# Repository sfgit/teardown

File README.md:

# teardown
Files from Crowdsupply Teardown 2018 EAGLE Presentation

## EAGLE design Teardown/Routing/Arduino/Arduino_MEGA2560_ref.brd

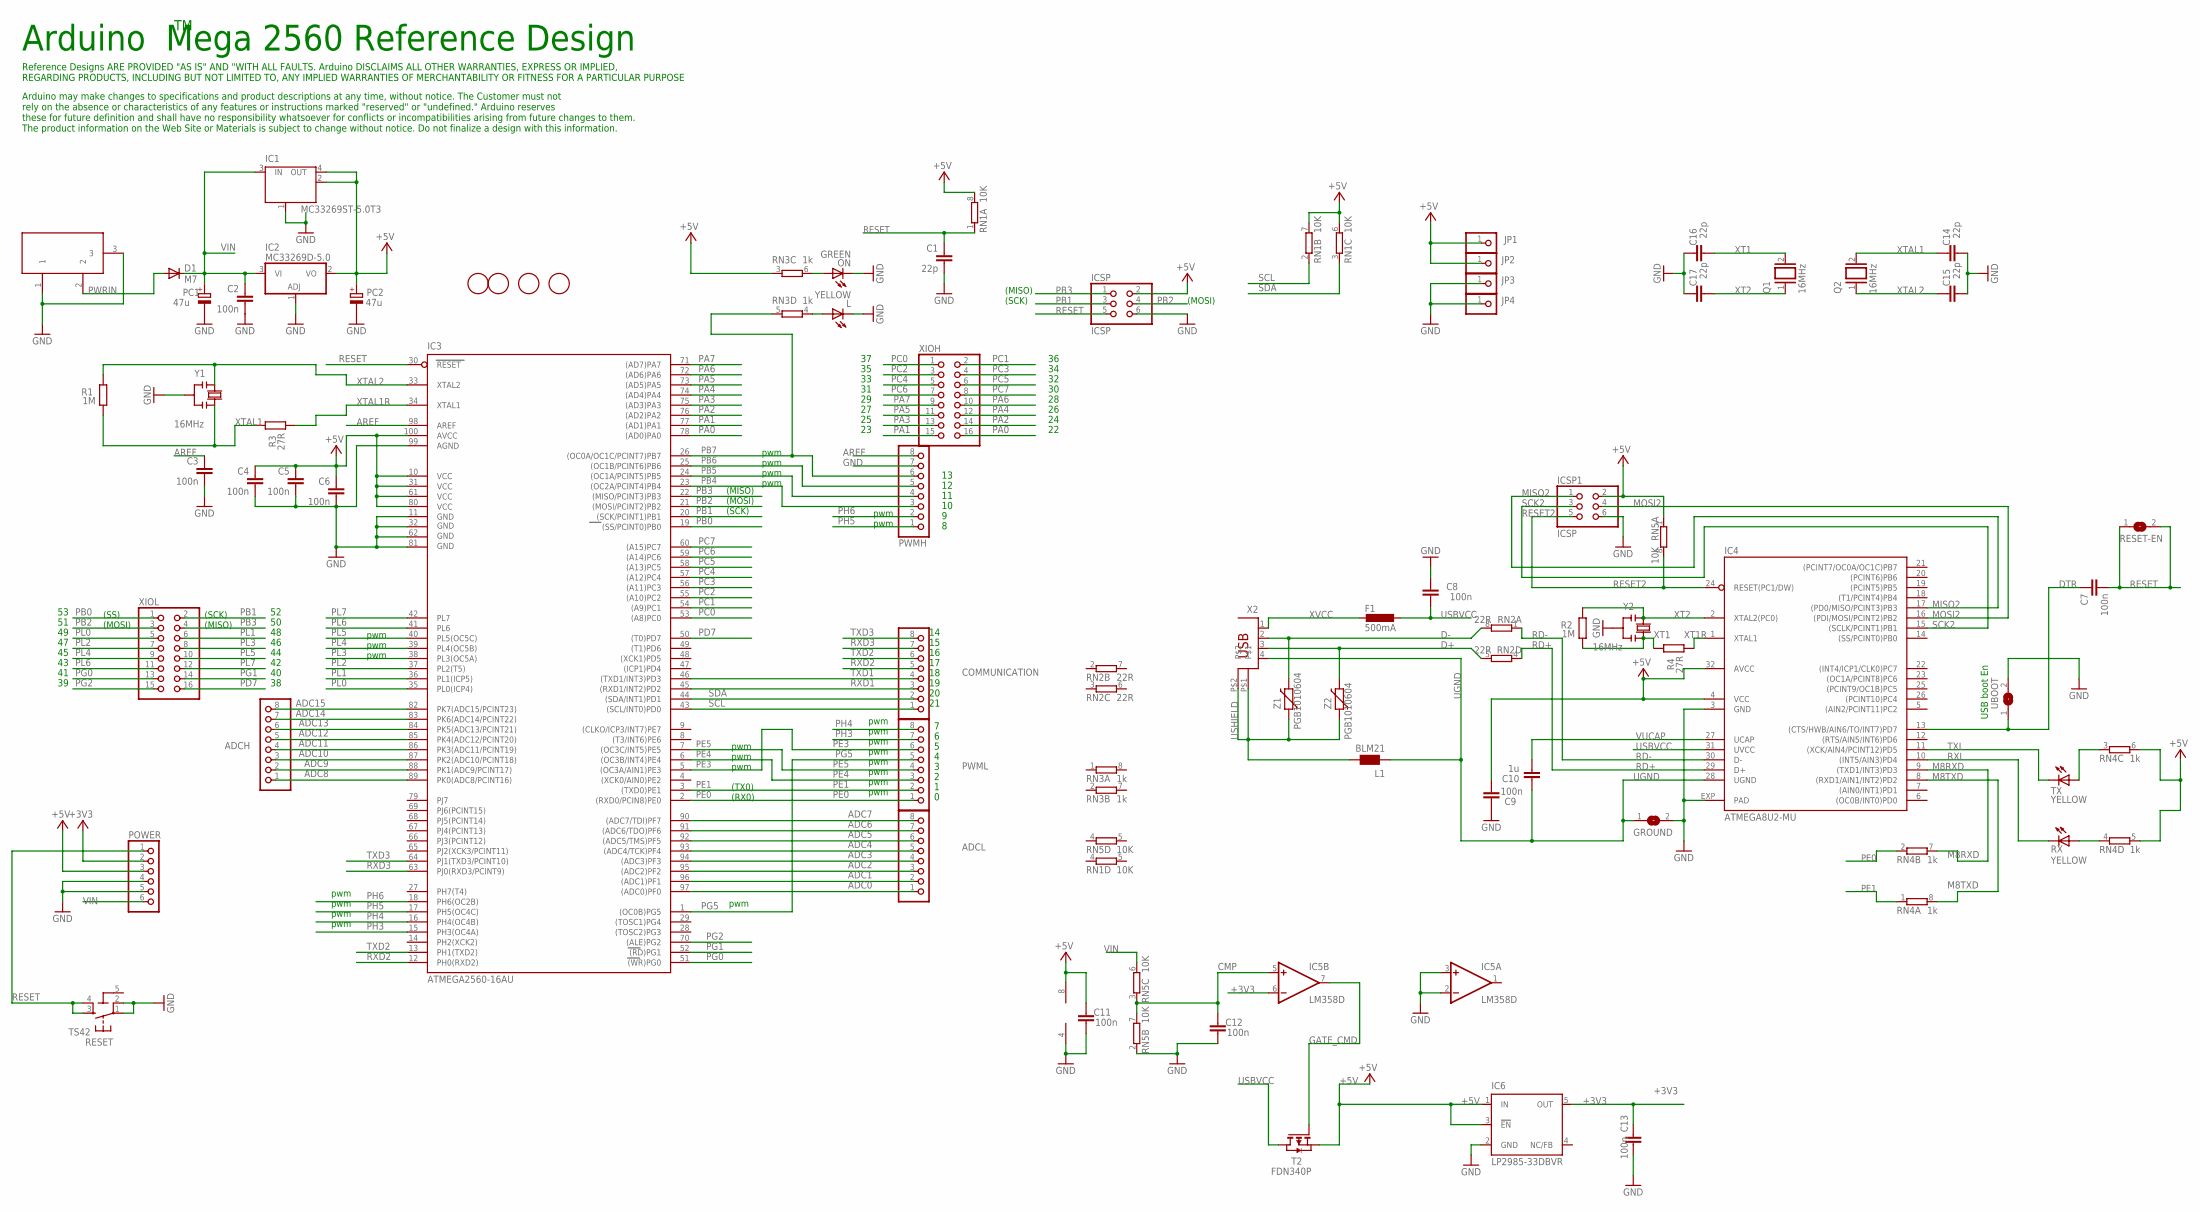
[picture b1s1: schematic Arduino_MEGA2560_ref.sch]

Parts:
ADCH: PINHD-1X8; 1X08
ADCL: PINHD-1X8; 1X08
C1, C14, C15, C16, C17: 22p; C0603-ROUND
C2, C3, C4, C5, C6, C7, C9, C12, C13: 100n; C0603-ROUND
C8, C11: 100n; C0603
C10: 1u; C0603-ROUND
COMMUNICATION: PINHD-1X8; 1X08
D1: M7; SMB
F1: 500mA; L1812
GROUND: SJ
IC1: MC33269ST-5.0T3; SOT223
IC2: MC33269D-5.0; DPACK
IC3: ATMEGA2560-16AU; TQFP100
IC4: ATMEGA8U2-MU; QFN32
IC5: LM358D; SO08
IC6: LP2985-33DBVR; SOT23-DBV
ICSP, ICSP1: ICSP; 2X03
JP1, JP2, JP3, JP4: PINHD-1X1; 1X01
L: YELLOW; CHIP-LED0805
L1: BLM21; 0805
ON: GREEN; CHIP-LED0805
PC1, PC2: 47u; PANASONIC_D
POWER: PINHD-1X6; 1X06
PWMH: PINHD-1X8; 1X08
PWML: PINHD-1X8; 1X08
Q1, Q2: 16MHz; QS
R1, R2: 1M; R0603-ROUND
R3, R4: 27R; R0603-ROUND
RESET: TS42
RESET-EN: SJ
RN1, RN5: 10K; CAT16
RN2: 22R; CAY16
RN3, RN4: 1k; CAY16
RX: YELLOW; CHIP-LED0805
T2: FDN340P; SOT-23
TX: YELLOW; CHIP-LED0805
U$2, U$3, U$4, U$5: FIDUCIALMOUNT; FIDUCIA-MOUNT
UBOOT: SJ
X1: DC21MMX; DC-21MM
X2: PN61729
XIOH: PINHD-2X8; 2X08
XIOL: PINHD-2X8; 2X08
Y1, Y2: 16MHz; RESONATOR
Z1, Z2: PGB1010604; CT/CN0603

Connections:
5-GND: RESET.5 (5-GND)
+3V3: C13.2, IC5.6 (-IN), IC6.5 (OUT), POWER.2
+5V: C4.1, C5.1, C6.1, C9.1, C11.2, IC1.2 (OUT), IC1.4 (OUT), IC2.2 (VO), IC3.10 (VCC), IC3.31 (VCC1), IC3.61 (VCC2), IC3.80 (VCC3), IC3.100 (AVCC), IC4.4 (VCC), IC4.32 (AVCC), IC5.8 (V+), IC6.1 (IN), IC6.3 (!EN), ICSP.2, ICSP1.2, JP1.1, JP2.1, PC2.+, POWER.3, RN1.6 (2), RN1.7 (2), RN1.8 (2), RN3.3 (1), RN4.5 (2), RN4.6 (2), RN5.1, T2.2 (S)
ADC0: ADCL.1, IC3.97 ((ADC0)PF0)
ADC1: ADCL.2, IC3.96 ((ADC1)PF1)
ADC2: ADCL.3, IC3.95 ((ADC2)PF2)
ADC3: ADCL.4, IC3.94 ((ADC3)PF3)
ADC4: ADCL.5, IC3.93 ((ADC4/TCK)PF4)
ADC5: ADCL.6, IC3.92 ((ADC5/TMS)PF5)
ADC6: ADCL.7, IC3.91 ((ADC6/TDO)PF6)
ADC7: ADCL.8, IC3.90 ((ADC7/TDI)PF7)
ADC8: ADCH.1, IC3.89 (PK0(ADC8/PCINT16))
ADC9: ADCH.2, IC3.88 (PK1(ADC9/PCINT17))
ADC10: ADCH.3, IC3.87 (PK2(ADC10/PCINT18))
ADC11: ADCH.4, IC3.86 (PK3(ADC11/PCINT19))
ADC12: ADCH.5, IC3.85 (PK4(ADC12/PCINT20))
ADC13: ADCH.6, IC3.84 (PK5(ADC13/PCINT21))
ADC14: ADCH.7, IC3.83 (PK6(ADC14/PCINT22))
ADC15: ADCH.8, IC3.82 (PK7(ADC15/PCINT23))
AREF: C3.1, IC3.98 (AREF), PWMH.8
CMP: C12.2, IC5.5 (+IN), RN5.3 (1), RN5.7 (2)
D+: RN2.5 (2), X2.3, Z2.2
D-: RN2.8 (2), X2.2, Z1.2
DTR: C7.1, IC4.13 ((CTS/HWB/AIN6/TO/INT7)PD7), UBOOT.1
GATE_CMD: IC5.7 (OUT), T2.3 (G)
GND: C1.2, C2.2, C3.2, C4.2, C5.2, C6.2, C8.2, C9.2, C11.1, C12.1, C13.1, C14.1, C15.1, C16.2, C17.2, GROUND.2, IC1.1 (GND/ADJ), IC2.1 (ADJ), IC3.11 (GND), IC3.32 (GND1), IC3.62 (GND2), IC3.81 (GND3), IC3.99 (AGND), IC4.3 (GND), IC4.EXP (PAD), IC5.2 (-IN), IC5.3 (+IN), IC5.4 (V-), IC6.2 (GND), ICSP.6, ICSP1.6, JP3.1, JP4.1, L.C, ON.C, PC1.-, PC2.-, POWER.4, POWER.5, PWMH.7, RESET.1, RESET.2, RN5.2 (1), UBOOT.2, X1.1, X1.3, Y1.2, Y2.2
M8RXD: IC4.9 ((TXD1/INT3)PD3), RN4.7 (2)
M8TXD: IC4.8 ((RXD1/AIN1/INT2)PD2), RN4.8 (2)
MISO2: IC4.17 ((PD0/MISO/PCINT3)PB3), ICSP1.1
MOSI2: IC4.16 ((PDI/MOSI/PCINT2)PB2), ICSP1.4
unnamed: L.A, RN3.4 (1)
unnamed: ON.A, RN3.6 (2)
unnamed: RN4.4 (1), RX.A
unnamed: RN4.3 (1), TX.A
PA0: IC3.78 ((AD0)PA0), XIOH.16
PA1: IC3.77 ((AD1)PA1), XIOH.15
PA2: IC3.76 ((AD2)PA2), XIOH.14
PA3: IC3.75 ((AD3)PA3), XIOH.13
PA4: IC3.74 ((AD4)PA4), XIOH.12
PA5: IC3.73 ((AD5)PA5), XIOH.11
PA6: IC3.72 ((AD6)PA6), XIOH.10
PA7: IC3.71 ((AD7)PA7), XIOH.9
PB0: IC3.19 ((SS/PCINT0)PB0), XIOL.1
PB1: IC3.20 ((SCK/PCINT1)PB1), ICSP.3, XIOL.2
PB2: IC3.21 ((MOSI/PCINT2)PB2), ICSP.4, XIOL.3
PB3: IC3.22 ((MISO/PCINT3)PB3), ICSP.1, XIOL.4
PB4: IC3.23 ((OC2A/PCINT4)PB4), PWMH.3
PB5: IC3.24 ((OC1A/PCINT5)PB5), PWMH.4
PB6: IC3.25 ((OC1B/PCINT6)PB6), PWMH.5
PB7: IC3.26 ((OC0A/OC1C/PCINT7)PB7), PWMH.6, RN3.5 (2)
PC0: IC3.53 ((A8)PC0), XIOH.1
PC1: IC3.54 ((A9)PC1), XIOH.2
PC2: IC3.55 ((A10)PC2), XIOH.3
PC3: IC3.56 ((A11)PC3), XIOH.4
PC4: IC3.57 ((A12)PC4), XIOH.5
PC5: IC3.58 ((A13)PC5), XIOH.6
PC6: IC3.59 ((A14)PC6), XIOH.7
PC7: IC3.60 ((A15)PC7), XIOH.8
PD7: IC3.50 ((T0)PD7), XIOL.16
PE0: IC3.2 ((RXD0/PCIN8)PE0), PWML.1, RN4.2 (1)
PE1: IC3.3 ((TXD0)PE1), PWML.2, RN4.1
PE3: IC3.5 ((OC3A/AIN1)PE3), PWML.6
PE4: IC3.6 ((OC3B/INT4)PE4), PWML.3
PE5: IC3.7 ((OC3C/INT5)PE5), PWML.4
PG0: IC3.51 ((WR)PG0), XIOL.13
PG1: IC3.52 ((RD)PG1), XIOL.14
PG2: IC3.70 ((ALE)PG2), XIOL.15
PG5: IC3.1 ((OC0B)PG5), PWML.5
PH3: IC3.15 (PH3(OC4A)), PWML.7
PH4: IC3.16 (PH4(OC4B)), PWML.8
PH5: IC3.17 (PH5(OC4C)), PWMH.1
PH6: IC3.18 (PH6(OC2B)), PWMH.2
PL0: IC3.35 (PL0(ICP4)), XIOL.5
PL1: IC3.36 (PL1(ICP5)), XIOL.6
PL2: IC3.37 (PL2(T5)), XIOL.7
PL3: IC3.38 (PL3(OC5A)), XIOL.8
PL4: IC3.39 (PL4(OC5B)), XIOL.9
PL5: IC3.40 (PL5(OC5C)), XIOL.10
PL6: IC3.41 (PL6), XIOL.11
PL7: IC3.42 (PL7), XIOL.12
PWRIN: D1.A, X1.2
RD+: IC4.29 (D+), RN2.4 (1)
RD-: IC4.30 (D-), RN2.1
RESET: C1.1, C7.2, IC3.30 (RESET), ICSP.5, POWER.1, RESET.3, RESET.4, RESET-EN.1, RESET-EN.2, RN1.1
RESET2: IC4.24 (RESET(PC1/DW)), ICSP1.5, RN5.8 (2)
RXD1: COMMUNICATION.3, IC3.45 ((RXD1/INT2)PD2)
RXD2: COMMUNICATION.5, IC3.12 (PH0(RXD2))
RXD3: COMMUNICATION.7, IC3.63 (PJ0(RXD3/PCINT9))
RXL: IC4.10 ((INT5/AIN3)PD4), RX.C
SCK2: IC4.15 ((SCLK/PCINT1)PB1), ICSP1.3
SCL: COMMUNICATION.1, IC3.43 ((SCL/INT0)PD0), RN1.2 (1)
SDA: COMMUNICATION.2, IC3.44 ((SDA/INT1)PD1), RN1.3 (1)
TXD1: COMMUNICATION.4, IC3.46 ((TXD1/INT3)PD3)
TXD2: COMMUNICATION.6, IC3.13 (PH1(TXD2))
TXD3: COMMUNICATION.8, IC3.64 (PJ1(TXD3/PCINT10))
TXL: IC4.11 ((XCK/AIN4/PCINT12)PD5), TX.C
UGND: C10.2, GROUND.1, IC4.28 (UGND), L1.1, X2.4
USBVCC: C8.1, F1.1, IC4.31 (UVCC), T2.1 (D)
USHIELD: L1.2, X2.P$1, X2.P$2, Z1.1, Z2.1
VIN: C2.1, D1.C, IC1.3 (IN), IC2.3 (VI), PC1.+, POWER.6, RN5.6 (2)
VUCAP: C10.1, IC4.27 (UCAP)
XT1: C16.1, Q1.2, R2.1, R4.2, Y2.3
XT1R: IC4.1 (XTAL1), R4.1
XT2: C17.1, IC4.2 (XTAL2(PC0)), Q1.1, R2.2, Y2.1
XTAL1: C14.2, Q2.2, R1.1, R3.2, Y1.3
XTAL1R: IC3.34 (XTAL1), R3.1
XTAL2: C15.2, IC3.33 (XTAL2), Q2.1, R1.2, Y1.1
XVCC: F1.2, X2.1

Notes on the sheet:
(SCK)
(MISO)
(MOSI)
pwm
(TX0)
(RX0)
(SS)
USB boot En
Arduino Mega 2560 Reference Design
Arduino may make changes to specifications and product descriptions at any time, without notice. The Customer must not rely on the absence or characteristics of any features or instructions marked "reserved" or "undefined." Arduino reserves these for future definition and shall have no responsibili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
Reference Designs ARE PROVIDED "AS IS" AND "WITH ALL FAULTS. Arduino DISCLAIMS ALL OTHER WARRANTIES, EXPRESS OR IMPLIED, REGARDING PRODUCTS, INCLUDING BUT NOT LIMITED TO, ANY IMPLIED WARRANTIES OF MERCHANTABILITY OR FITNESS FOR A PARTICULAR PURPOSE

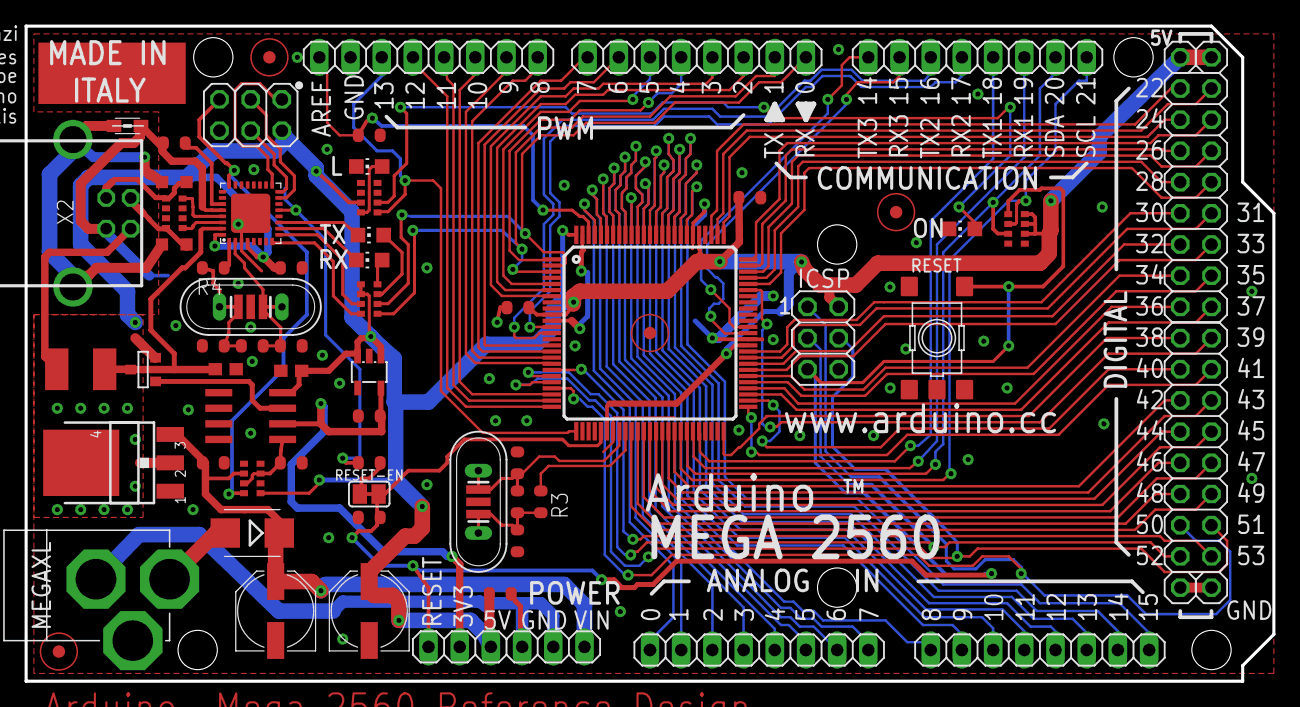
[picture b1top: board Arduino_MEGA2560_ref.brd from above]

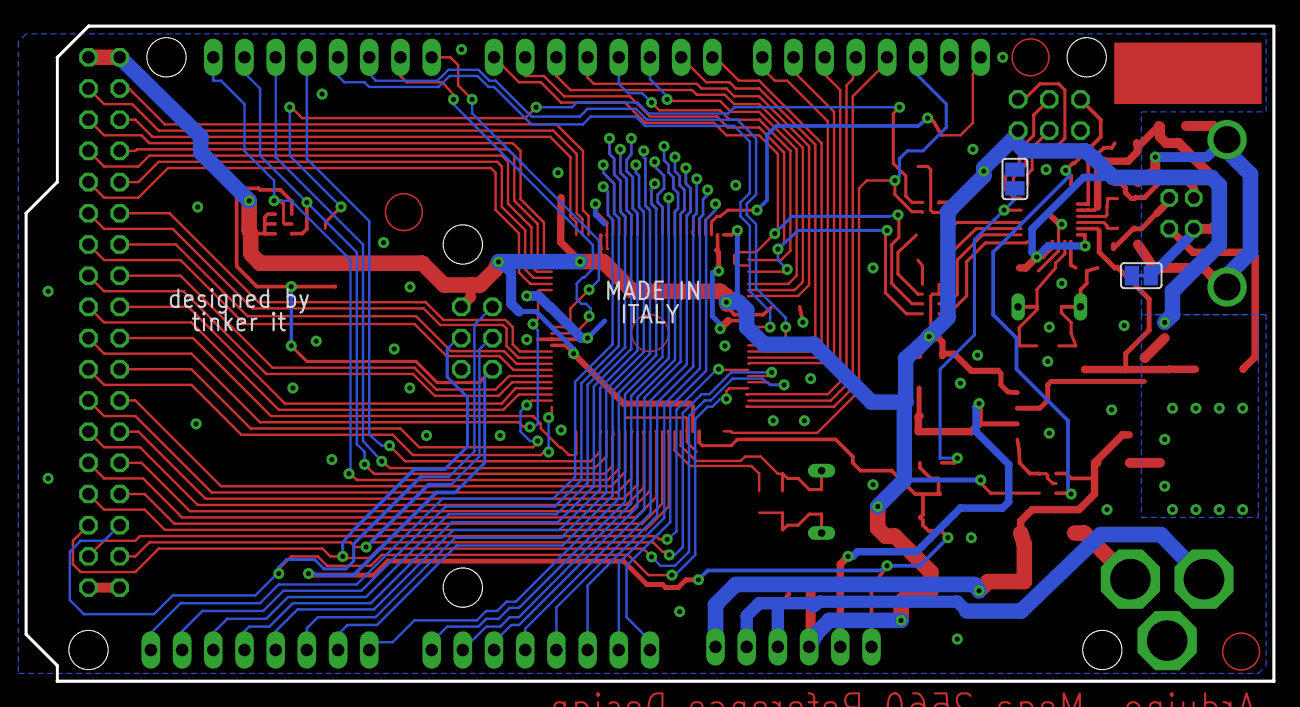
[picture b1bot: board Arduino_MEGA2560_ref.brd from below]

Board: 2 copper layers, 101.6 x 53.3 mm, 72 parts (2 on the bottom side), 107 nets.

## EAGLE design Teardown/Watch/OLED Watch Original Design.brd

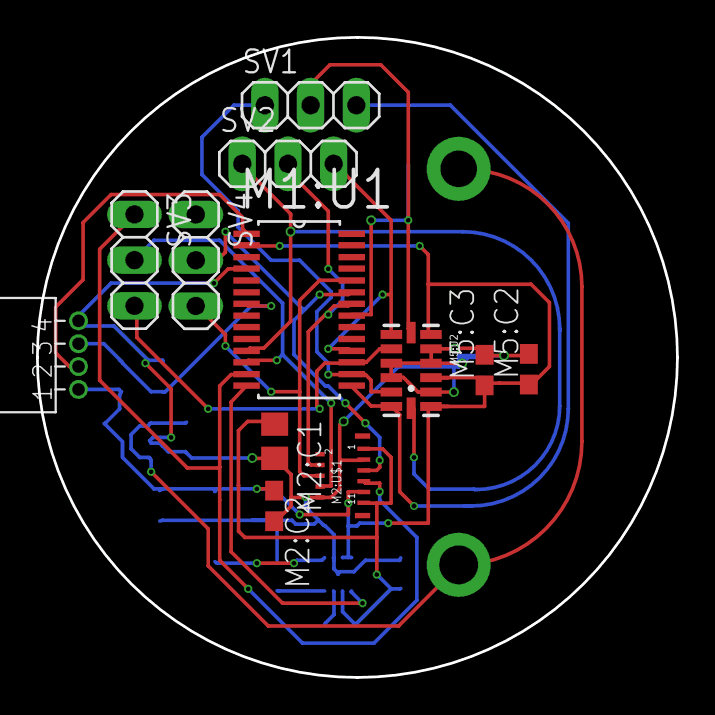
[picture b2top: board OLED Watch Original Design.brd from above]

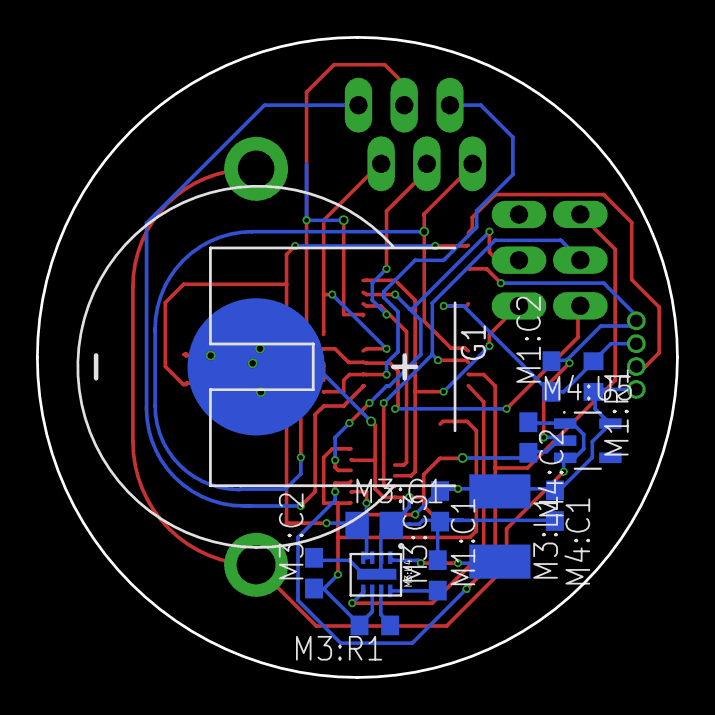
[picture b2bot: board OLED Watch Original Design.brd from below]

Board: 2 copper layers, 35.6 x 35.6 mm, 25 parts (13 on the bottom side), 21 nets.

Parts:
G1: CR2025H
J1: 851-87-004-20-001101
M1:C1, M5:C3: 0.1uF/16V; C0603
M1:C2: NP; C0603
M1:R1: 47k; R0603
M1:U1: MSP430F2132TPW; SOP-28N
M2:C1, M3:C1: 4.7uF/25V; C0805
M2:C2, M4:C1, M4:C2: 1uF/16V; C0603
M2:U$1: USMP-P24701
M3:C2: 2.2uF/16V; C0603
M3:C3: 0.22uF/16V; C0603
M3:L1: 15uH; L1812
M3:R1: 1.74M; R0603
M3:U4: LT3494; DFN8-3X2-DDB
M4:U5: TLV70030DDCR; SOT95P280X110-5
M5:C2: 10uF/16V; C0603
M5:U2: LIS302DLTR; LGA-14
SV1, SV2, SV3, SV4: 1X03

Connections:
CS_ACCEL: M1:U1.21, M5:U2.7, SV1.2
CS_DISPLAY: M1:U1.22, M2:U$1.4, SV2.2
DC_DISPLAY: M1:U1.24, M2:U$1.6, SV4.3
EN_DISP_PWR: M1:U1.14, M3:U4.5
GND: G1.3, J1.4, M1:C1.2, M1:C2.2, M1:U1.4, M2:C1.2, M2:C2.2, M2:U$1.3, M2:U$1.10, M3:C1.2, M3:C2.2, M3:C3.2, M3:U4.2, M3:U4.9, M4:C1.2, M4:C2.2, M4:U5.2, M5:C2.2, M5:C3.2, M5:U2.2, M5:U2.4, M5:U2.5, M5:U2.10, M5:U2.11
INT1: M1:U1.18, M5:U2.8, SV2.3
INT2: M1:U1.17, M5:U2.9, SV3.3
M3:N$1: M3:L1.2, M3:U4.1
M3:N$2: M3:C3.1, M3:U4.8
M3:N$4: M3:R1.1, M3:U4.7
RST_DISPLAY: M1:U1.23, M2:U$1.5, SV4.2
SBWTCK: J1.2, M1:U1.1
SBWTDIO: J1.3, M1:C2.1, M1:R1.1, M1:U1.7
SCLK_DISPLAY: M1:U1.13, M2:U$1.7, SV3.1
SDIN_DISPLAY: M1:U1.12, M2:U$1.8, SV3.2
SDI_ACCEL: M1:U1.15, M5:U2.13, SV1.3
SDO_ACCEL: M1:U1.16, M5:U2.12, SV1.1
SPC_ACCEL: M1:U1.11, M5:U2.14, SV2.1
VBAT: G1.1, G1.2, M4:C2.1, M4:U5.1, M4:U5.3
VCC_DISPLAY: M2:C1.1, M2:U$1.1, M2:U$1.11, M3:C2.1, M3:R1.2, M3:U4.6
VDD: J1.1, M1:C1.1, M1:R1.2, M1:U1.2, M2:C2.1, M2:U$1.9, M3:C1.1, M3:L1.1, M3:U4.3, M3:U4.4, M4:C1.1, M4:U5.5, M5:C2.1, M5:C3.1, M5:U2.1, M5:U2.3, M5:U2.6

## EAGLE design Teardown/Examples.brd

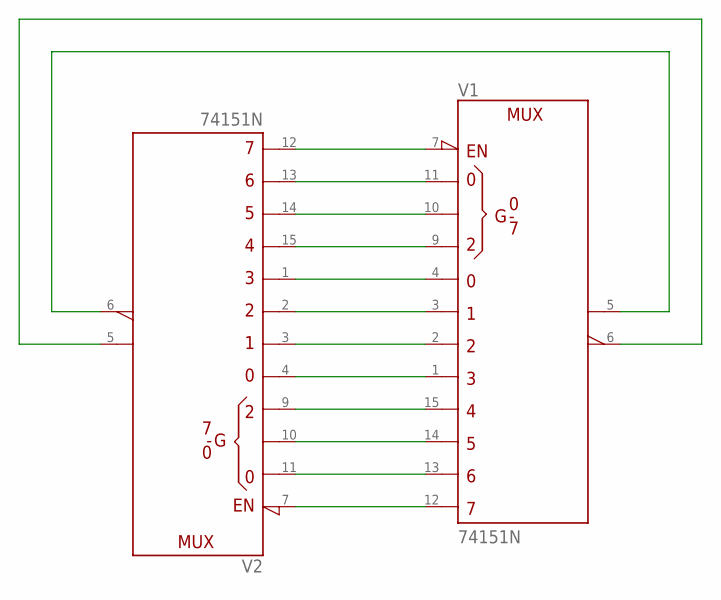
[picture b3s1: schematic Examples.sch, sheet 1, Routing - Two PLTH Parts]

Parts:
V1, V2: 74151N; DIL16

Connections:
+UB: V1.16 (+UB), V2.16 (+UB)
-UB: V1.8 (-UB), V2.8 (-UB)
unnamed: V1.7 (!G), V2.12 (D7)
unnamed: V1.11 (A), V2.13 (D6)
unnamed: V1.10 (B), V2.14 (D5)
unnamed: V1.9 (C), V2.15 (D4)
unnamed: V1.4 (D0), V2.1 (D3)
unnamed: V1.3 (D1), V2.2 (D2)
unnamed: V1.2 (D2), V2.3 (D1)
unnamed: V1.1 (D3), V2.4 (D0)
unnamed: V1.15 (D4), V2.9 (C)
unnamed: V1.14 (D5), V2.10 (B)
unnamed: V1.13 (D6), V2.11 (A)
unnamed: V1.12 (D7), V2.7 (!G)
unnamed: V1.5 (Y), V2.6 (W)
unnamed: V1.6 (W), V2.5 (Y)

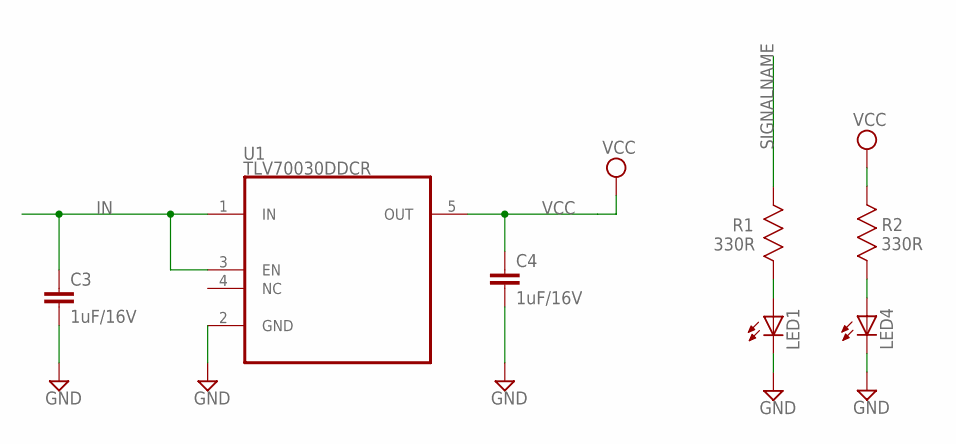
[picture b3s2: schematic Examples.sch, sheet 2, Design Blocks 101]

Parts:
C3, C4: 1uF/16V; C0603; DIGIKEY 399-8001-1-ND
LED1, LED4: LEDCHIP-LED0603; CHIP-LED0603
R1, R2: 330R; RESC1608X60N
U1: TLV70030DDCR; SOT95P280X110-5

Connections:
GND: C3.2, C4.2, LED1.C, LED4.C, U1.2 (GND); also elsewhere on the board
IN: C3.1, U1.1 (IN), U1.3 (EN)
unnamed: LED1.A, R1.2 (R2)
unnamed: LED4.A, R2.2 (R2)
SIGNALNAME: R1.1 (R1)
VCC: C4.1, R2.1 (R1), U1.5 (OUT); also elsewhere on the board

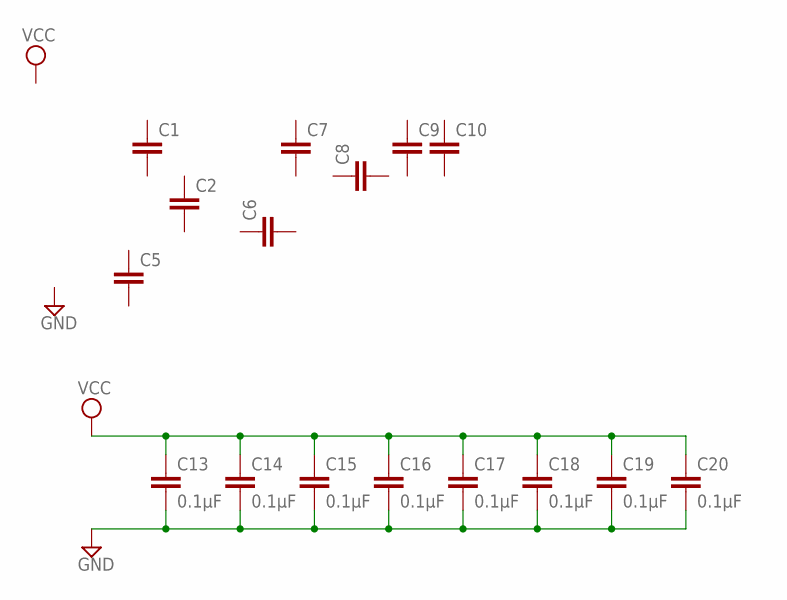
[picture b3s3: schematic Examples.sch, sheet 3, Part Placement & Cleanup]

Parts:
C1, C2, C5, C6, C7, C8, C9, C10: C-EUC0603; C0603
C13, C14, C15, C16, C17, C18, C19, C20: 0.1µF; C0603

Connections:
GND: C13.2, C14.2, C15.2, C16.2, C17.2, C18.2, C19.2, C20.2; also elsewhere on the board
VCC: C13.1, C14.1, C15.1, C16.1, C17.1, C18.1, C19.1, C20.1; also elsewhere on the board

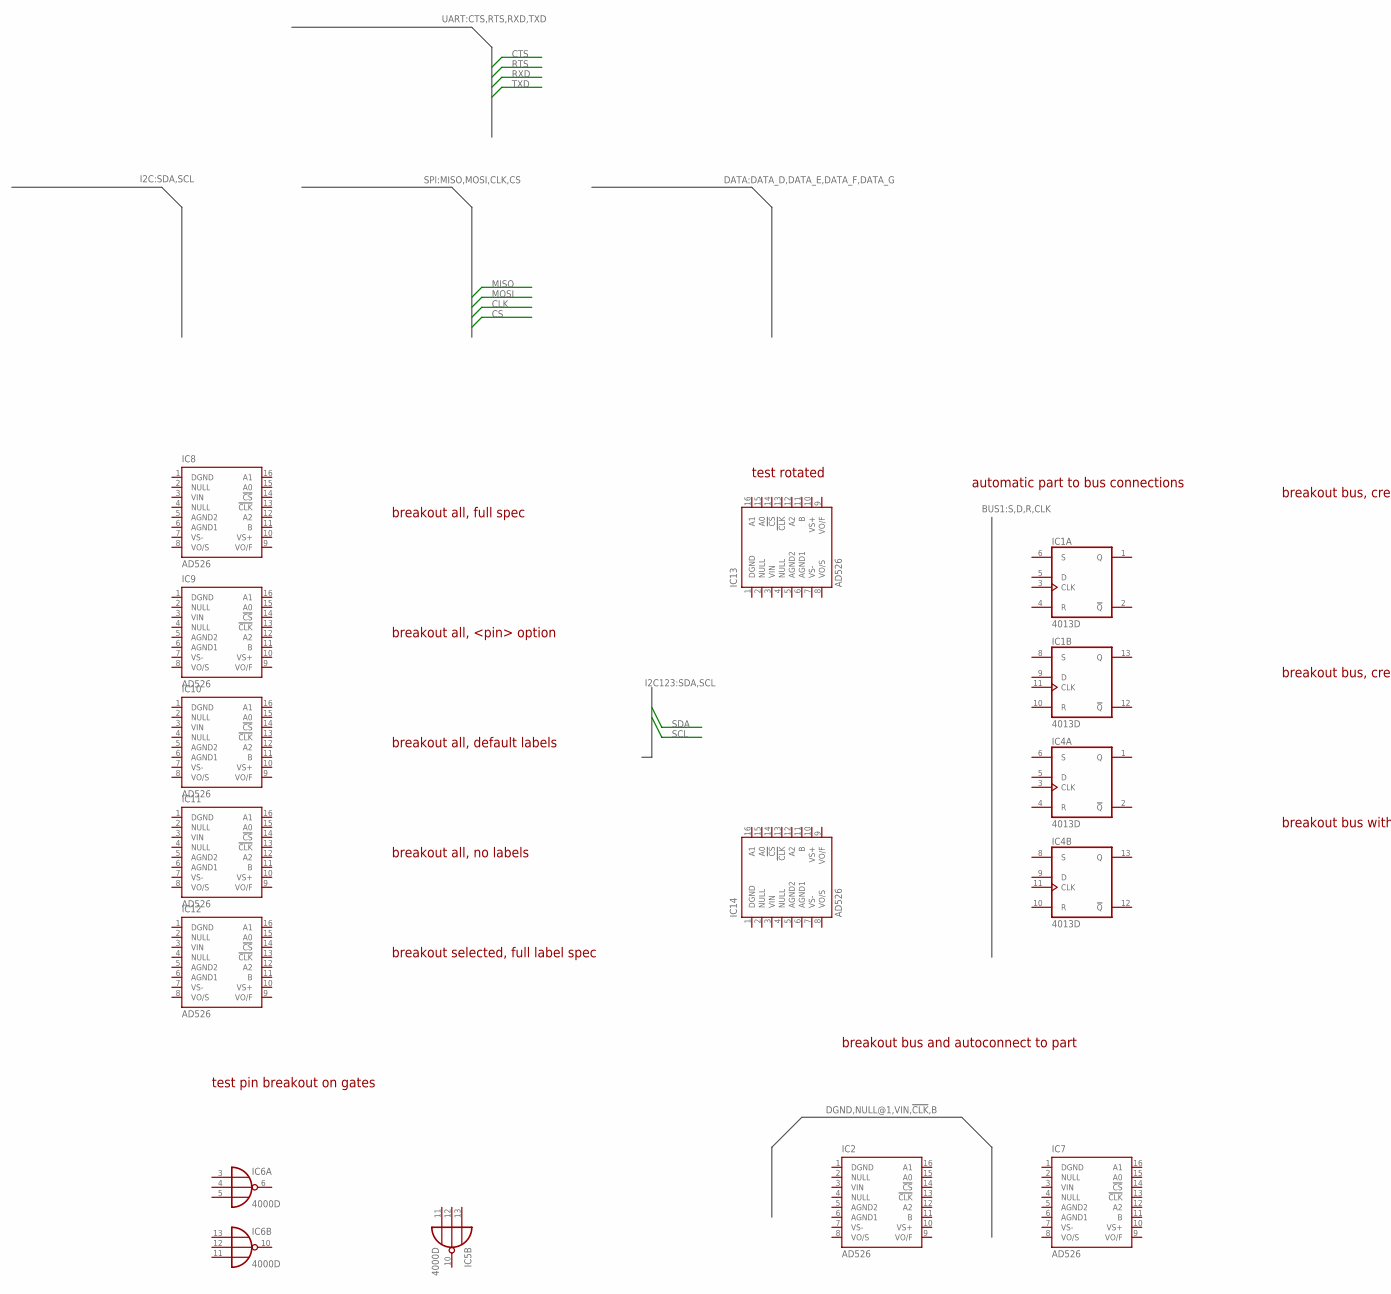
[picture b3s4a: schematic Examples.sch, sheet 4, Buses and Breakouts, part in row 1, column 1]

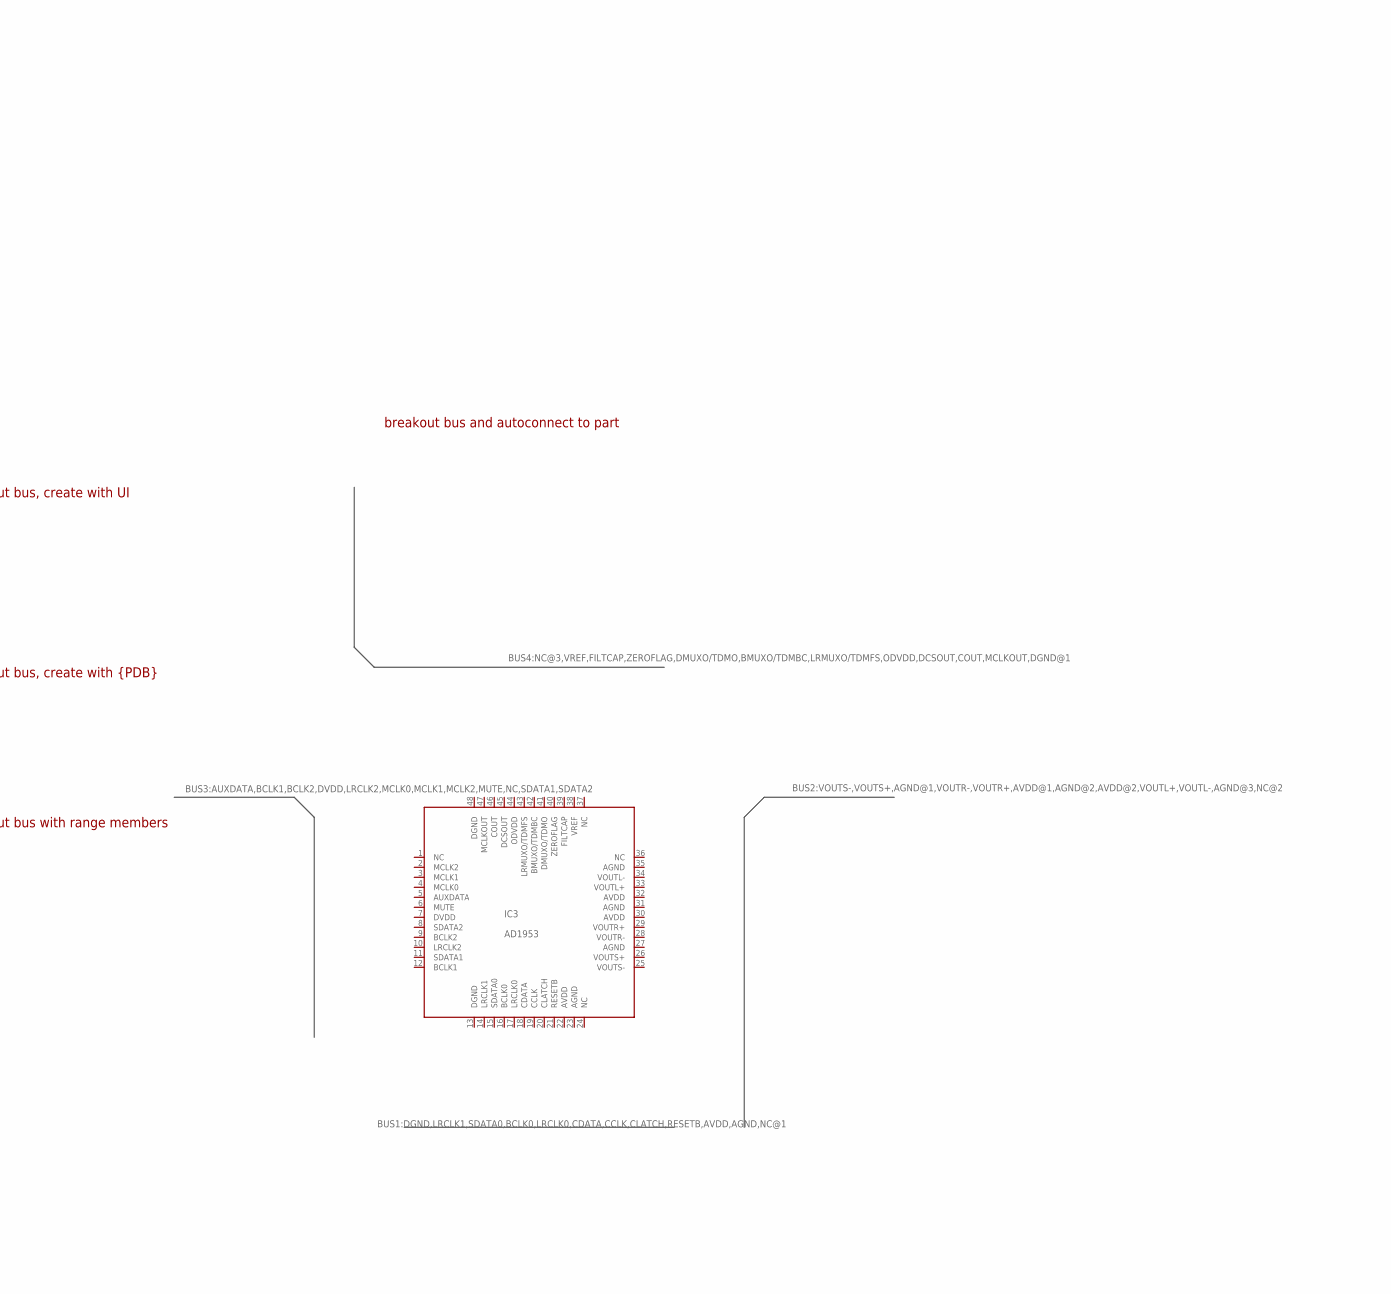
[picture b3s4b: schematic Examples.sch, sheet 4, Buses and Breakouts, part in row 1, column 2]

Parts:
IC1, IC4: 4013D; SO14
IC2, IC7, IC8, IC9, IC10, IC11, IC12, IC13, IC14: AD526; DIL16
IC3: AD1953; QFP-7X7-48
IC5, IC6: 4000D; SO14

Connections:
AGND: IC3.23 (AGND), IC3.27 (AGND), IC3.31 (AGND), IC3.35 (AGND)
AVDD: IC3.22 (AVDD), IC3.30 (AVDD), IC3.32 (AVDD)
DGND: IC3.13 (DGND), IC3.48 (DGND)
DVDD: IC3.7 (DVDD)
ODVDD: IC3.44 (ODVDD)
VDD: IC1.14 (VDD), IC4.14 (VDD), IC5.14 (VDD), IC6.14 (VDD)
VSS: IC1.7 (VSS), IC4.7 (VSS), IC5.7 (VSS), IC6.7 (VSS)

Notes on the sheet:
breakout all, full spec
breakout all, <pin> option
breakout all, default labels
breakout all, no labels
breakout selected, full label spec
automatic part to bus connections
test rotated
test pin breakout on gates
breakout bus, create with {PDB}
breakout bus, create with UI
breakout bus with range members
breakout bus and autoconnect to part

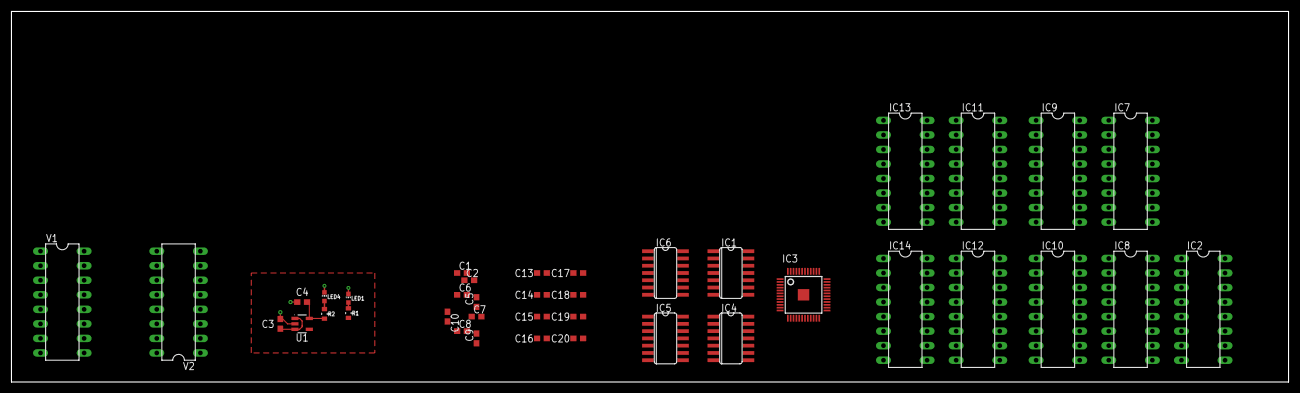
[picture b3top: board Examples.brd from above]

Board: 2 copper layers, 223.2 x 64.8 mm, 39 parts (0 on the bottom side), 26 nets.
